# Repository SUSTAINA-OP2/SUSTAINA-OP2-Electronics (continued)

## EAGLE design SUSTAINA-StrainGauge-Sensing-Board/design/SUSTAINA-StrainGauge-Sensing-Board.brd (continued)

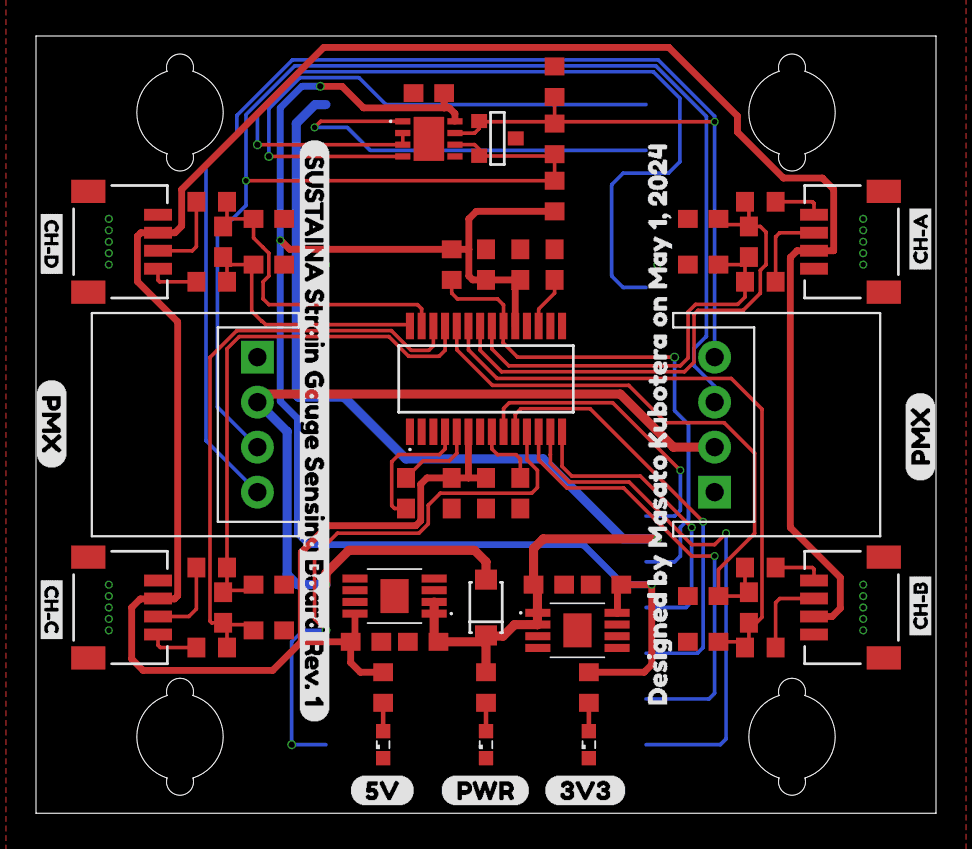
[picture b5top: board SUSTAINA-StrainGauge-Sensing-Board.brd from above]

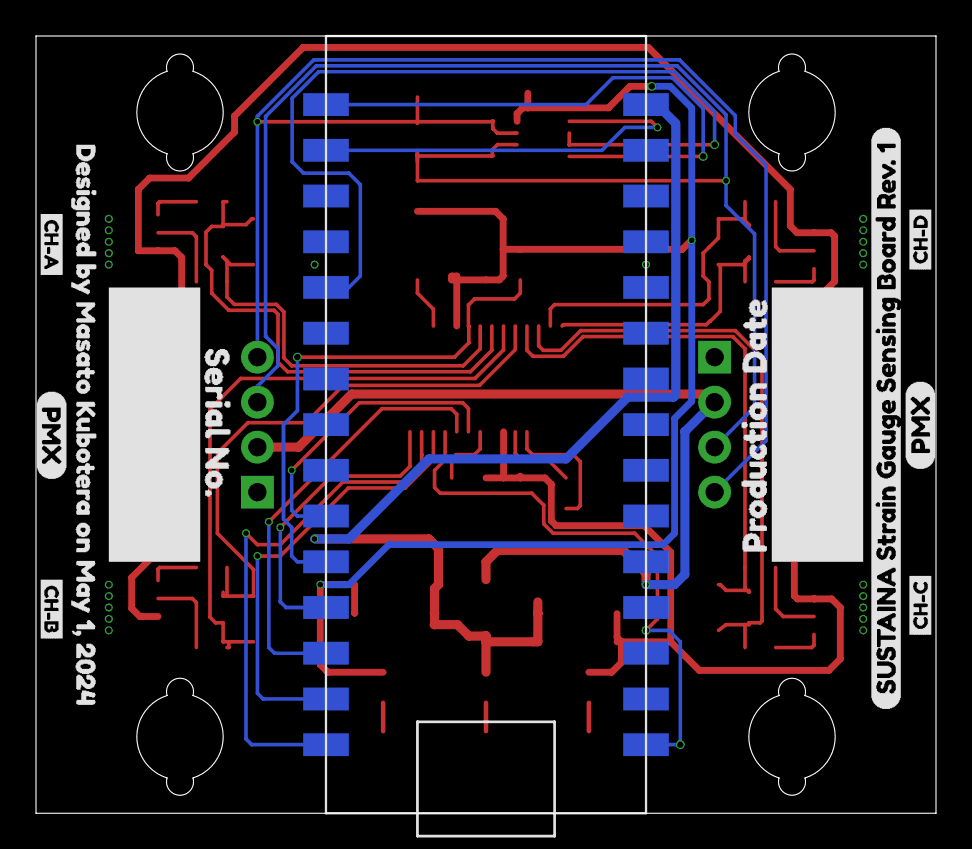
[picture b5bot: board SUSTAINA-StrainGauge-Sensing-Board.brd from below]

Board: 2 copper layers, 50.0 x 43.2 mm, 76 parts (11 on the bottom side), 40 nets.

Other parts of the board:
U$1: PWR
U$2: 3V3
U$3, U$17: CH#B0
U$4, U$18: CH#A0
U$5, U$14: CH#C0
U$6, U$15: CH#D0
U$7, U$8, U$16, U$19: PMX
U$9: 5V
U$10, U$13: DESIGNED_BY_MASATO_KUBOTERA_ON_MAY_1
U$11, U$12: SUSTAINA_STRAIN_GAUGE_SENSING_BOARD_REV#_1
U$20: SERIAL_NO#0
U$21: PRODUCTION_DATE0

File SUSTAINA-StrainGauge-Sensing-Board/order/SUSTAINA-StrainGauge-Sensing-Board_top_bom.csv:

Comment,Designator,Footprint,LCSC Part #
CDSOT23-SM712,D2 ,CDSOT23-SM712,C404012
0.1u,C5 C19 C24,C0603,C80516
1k,R2 R3 R7 R8 R9 R10 R11 R12 R13 R14 R15,R0603,C22548
1n,C6 C7 C8 C9 C10 C11 C12 C13 C14 C15 C16 C17,C0603,C153291
1u,C18 C20 C21 C23,C0603,C431003
2k,R1,R0603,C105576
4.7n,C22,C0603,C2180681
10u,C1 C2 C3 C4,C0603,C86275
120,R5,R0603,C114640
680,R4 R6,R0603,C112310
ADS1262,IC4,SOP65P640X120-28N,C2669963
Green,LED1 LED2 LED3,SML0603,C2922668
SM04B-SRSS-TB,CH1 CH2 CH3 CH4,SM04B-SRSS-TB,C160404
SN65HVD75DRBR,IC3,SON65P300X300X100-9N,C98708
SS34FA,D1,SS34FA,C719833
TPS7B82-Q1,IC1,SOP65P490X110-9N,C5220182
TPS7B82-Q1,IC2,SOP65P490X110-9N,C424924
